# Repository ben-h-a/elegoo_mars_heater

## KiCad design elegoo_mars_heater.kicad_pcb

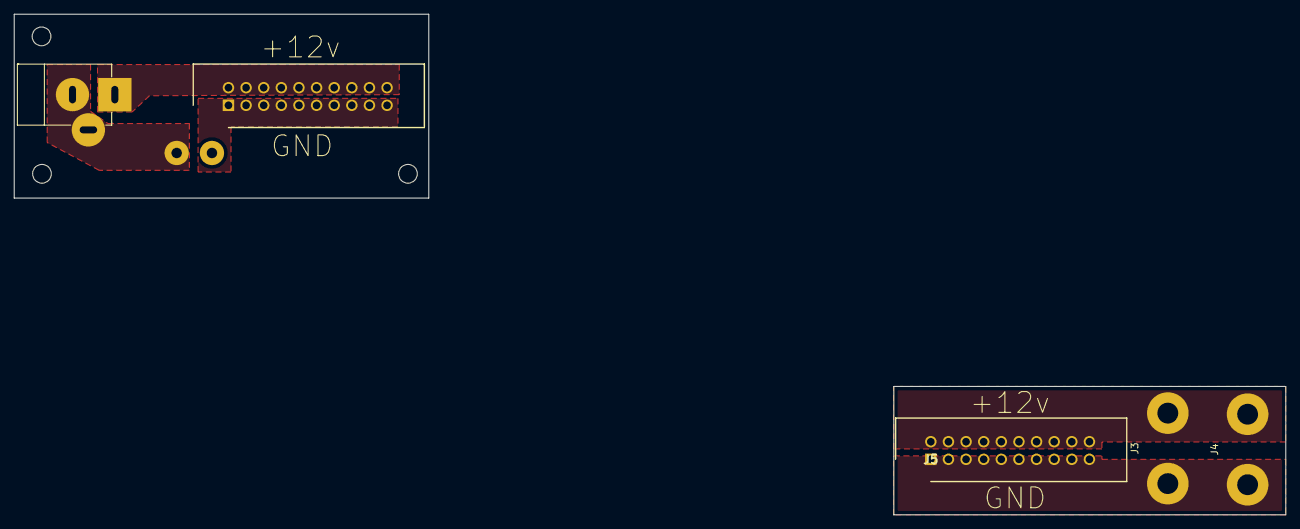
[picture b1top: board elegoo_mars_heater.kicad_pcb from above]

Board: 2 copper layers, 183.3 x 72.2 mm, 6 parts (0 on the bottom side), 5 nets.

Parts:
J1: Jack-DC; JACK_ALIM
J2, J5: T821120A1S100CEU; SHDR20W64P254X254_2X10_3302X895X915P
J3, J4: Conn_01x02_Female; solder_wire_pad-2x1-1mm_separate_nets
SW1: SW_DIP_x01; SolderWirePad_2x_1-5mmDrill

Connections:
+12V: J1.1, J2.2, J2.4, J2.6, J2.8, J2.10, J2.12, J2.14, J2.16, J2.18, J2.20
unnamed: J1.2, J1.3, SW1.1
unnamed: J2.1, J2.3, J2.5, J2.7, J2.9, J2.11, J2.13, J2.15, J2.17, J2.19
unnamed: J3.1, J4.1, J5.1, J5.3, J5.5, J5.7, J5.9, J5.11, J5.13, J5.15, J5.17, J5.19
unnamed: J3.2, J4.2, J5.2, J5.4, J5.6, J5.8, J5.10, J5.12, J5.14, J5.16, J5.18, J5.20
